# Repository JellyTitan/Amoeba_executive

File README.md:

# Amoeba KingPin (formerly Ameoba Executive)
## **This is a work in progress and should not go into production!**

Ameoba Single key PCB variant designed for simplicity and easy building.

The amoeba pcb family is often used in ergonomic split keyboards. 
Most amoeba variants are overly complex and difficult to solder. 
This variant leverages the parallel relationship of rows, columns, and the VCC & GND nets to simplify the layout. Adds support for SMD or through-hole diodes.

Designed for staggered pin soldering and jumper wire connections for super easy builds.
All the pin holes are spaced at 2.54mm, so a breadboard can be used as an assembly jig.

@todo
* ~~Pick a lane - multi-up snip-apart for 100x100 pre wired pcb, or single key outline for jlcpcb multi-up. (Second one  seems best) ("Member of the board" joke may not work - maybe change the name?)~~
* Add simple explanation of 1-many, net, and serial LED on front side
* Pin markings on backside
* Should via go through the pad?
* ~~Migrate footprint and symbol libraries~~
* add credit for sofle symbols.
* ~~Add 2.2 mm screw holes on corners?~~
* Add pin crown logo
* Validate the markings are legible at scale.
* Maybe remove text and replace with symbols? (-/+ IN/OUT)
* Change topside pad shapes to mirror earlier variants with arrows.
* jlcpcb charges extra for 5x5 layout - can this layout be embedded in the repo?
* Add .step 3d part files to kicad mockup.
* Validate the new name "KingPin" is acceptable, and change the name across the repo.

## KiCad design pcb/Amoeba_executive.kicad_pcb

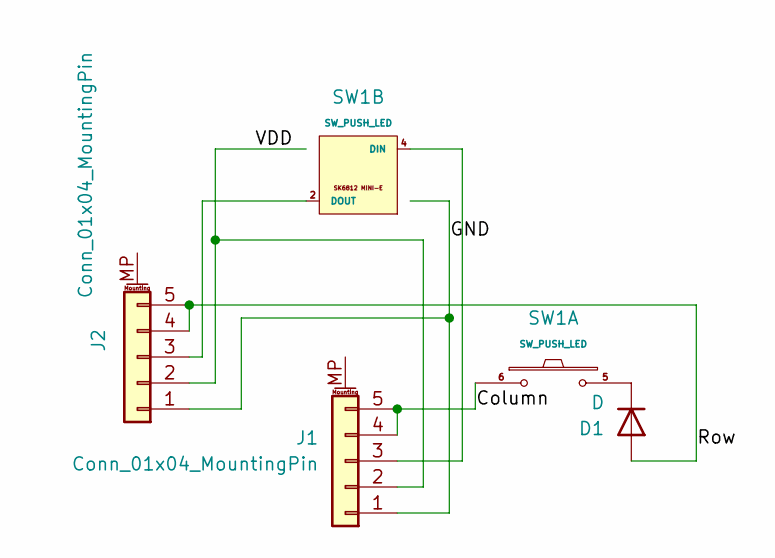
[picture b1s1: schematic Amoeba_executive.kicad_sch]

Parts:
D1: D; D_SOD-123_DO-35_Hybrid_Single_sided
J1, J2: Conn_01x04_MountingPin; amoeba_executive_5pinn_conn
SW1: SW_PUSH_LED; amoeba_executive_V4

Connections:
/Column: J1.4, J1.5, SW1.6
/Row: D1.2 (A), J2.4, J2.5
GND: J1.1, J2.1, SW1.3 (GND)
unnamed: D1.1 (K), SW1.5
unnamed: J1.3, SW1.4 (DIN)
unnamed: J2.3, SW1.2 (DOUT)
VDD: J1.2, J2.2, SW1.1 (VDD)

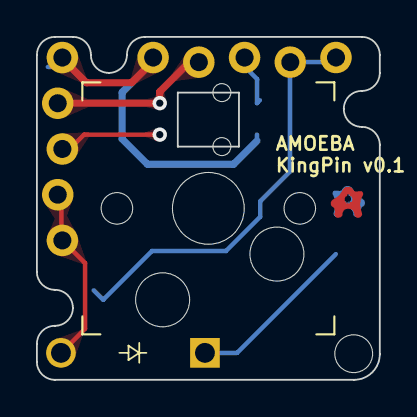
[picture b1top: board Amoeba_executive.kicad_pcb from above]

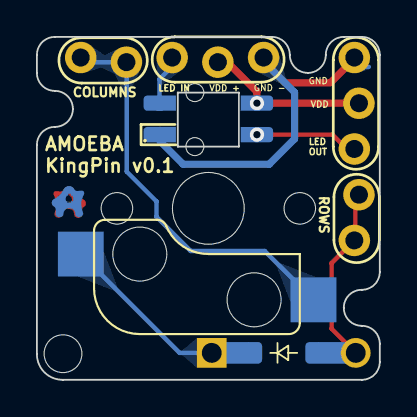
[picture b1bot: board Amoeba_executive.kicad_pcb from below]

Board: 2 copper layers, 19.1 x 19.0 mm, 6 parts (2 on the bottom side), 7 nets.

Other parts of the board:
Amoeba-Logo-Small: G***; amoeba-logo-small
Amoeba-Logo-Small#2: G***; amoeba-logo-small

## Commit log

2023-04-15 Updated readme added image updated folder structure to seperate pcb
2023-04-16 two sets of 5 pins
2023-04-16 First draft complete
2023-04-16 Created footprint library consolidated footprints in new library adjusted pads for single sided diodes
2023-04-17 SENT OUT FOR PRODUCTION Added basic branding Generated gerbers
2023-04-17 Updated docs
